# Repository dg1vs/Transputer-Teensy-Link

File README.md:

# Transputer Teensy Link

A family of practical, Ethernet-connected link interfaces for classic INMOS transputer systems, based on the Teensy 4.1.

The project provides three hardware variants, a common firmware platform, and compatibility with host tools using the INMOS B300/TCPlink protocol.

> **Project status:** All three interfaces are in active use. They are experimental retrocomputing hardware and may still contain minor hardware or firmware quirks. Enclosures have not yet been designed.

## Why transputers are still interesting in 2026

Transputers remain fascinating devices even in 2026.

They combine a processor, local memory, hardware-assisted process scheduling, and fast point-to-point communication links. A transputer was intended to be used as a building block in a larger network of cooperating processors rather than as the single centre of a computer.

Together with occam and its CSP-inspired programming model, transputers provide a very direct platform for studying:

- concurrent and parallel programming;
- message passing;
- distributed systems;
- deterministic communication;
- hardware-supported process scheduling;
- processor networks without a shared system bus.

Many of these ideas are still relevant in modern many-core processors, network-on-chip architectures, distributed services, and accelerator systems.

The difficult part today is often not finding an interesting transputer board. The practical problem is finding a convenient interface between a modern computer and the transputer link.

## Design goals

A useful modern transputer link interface should ideally be:

- **Fast** — supporting the maximum 20 Mbit/s link speed.
- **Standards-based** — using a documented and already supported host interface.
- **Galvanically isolated** — at least between the development computer and the adapter.
- **Cross-platform** — usable from Linux, macOS, Windows, and other systems.
- **Based on available components** — without requiring rare historical devices such as the INMOS C011.
- **Practical** — compact, robust, and easy to connect to different target systems.

The use of Ethernet provides a standard host connection and, with normal Ethernet magnetics, galvanic isolation between the host network and the adapter.

The current transputer-side interfaces are single-ended and share their electrical reference with the target system. Full galvanic isolation of the transputer link itself is therefore a possible future improvement rather than a feature of the current boards.

## Project history

Andre Saischowa created the first prototype using a Teensy 4.1 together with an INMOS C011 link adapter.

The article [Putting A Teensy To Task As A Transputer Link](https://hackaday.com/2025/10/20/putting-a-teensy-to-task-as-a-transputer-link/) described how the Teensy 4.1 UART can implement the unusual transputer link framing directly. This led to a substantial extension of the firmware and made it possible to operate a transputer link without a C011.

Karsten Schmidt, DG1VS, designed the printed circuit boards. Andre is the author and maintainer of the Teensy Link software and continued to develop and improve the firmware.

The result is a common software platform supporting both the traditional C011 approach and direct Teensy-to-transputer communication.

## System overview

```mermaid
flowchart LR
    HOST["Host computer<br/>Linux, macOS, Windows, ..."]
    ETH["Ethernet / TCP/IP<br/>B300-compatible Linkops service"]
    T41["Teensy 4.1"]
    PHY["C011 or direct<br/>transputer link"]
    TARGET["Transputer system"]

    HOST <--> ETH
    ETH <--> T41
    T41 <--> PHY
    PHY <--> TARGET
```

The firmware obtains its IP address using DHCP and provides a B300-compatible service on TCP port **4047**.

The current firmware also contains:

- a small status web server on TCP port **80**;
- a network throughput test service on TCP port **4040**;
- optional SSD1306 OLED status output;
- experimental USB host, USB MIDI, and link-audio functions.

The additional USB and audio functions are not required for normal B300 link operation.

## Hardware variants

The KiCad hardware projects are located below [`hardware/`](hardware/).

### A. `link_teensy` — C011 and direct Teensy Link

Directory: [`hardware/link_teensy/`](hardware/link_teensy/)

This is the most complete board and contains both:

- a traditional INMOS C011 link interface;
- a direct Teensy 4.1 transputer link interface.

```mermaid
flowchart LR
    HOST["Ethernet host"] <--> T41["Teensy 4.1"]
    T41 --> C011["INMOS C011"]
    T41 --> DIRECT["Direct Teensy Link"]
    C011 --> TARGET["Transputer system"]
    DIRECT --> TARGET
```

This board is useful as:

- the original development platform;
- a C011 reference implementation;
- a comparison between C011 and direct UART-based link handling;
- a flexible laboratory interface.

The main disadvantage of the C011 path is its dependency on a historical component that is increasingly difficult to obtain.

### B. `link_teensy_small` — compact direct link

Directory: [`hardware/link_teensy_small/`](hardware/link_teensy_small/)

This is a smaller board that connects the Teensy 4.1 directly to the transputer link without requiring a C011.

```mermaid
flowchart LR
    HOST["Ethernet host"] <--> T41["Teensy 4.1"]
    T41 <--> TARGET["Transputer system"]
```

This is currently the most frequently used interface.

Its advantages include:

- no historical link-adapter IC;
- fewer components;
- compact construction;
- direct 20 Mbit/s operation;
- a 10-pin target connector carrying the link and subsystem control signals.

The target connector includes:

- `LinkIn`
- `LinkOut`
- `notReset`
- `notAnalyse`
- `notError`
- supply and ground connections

Always verify the exact connector orientation and board revision before connecting a target.

### C. `link_teensy_fpga` — direct link with PMOD adapter

Directory: [`hardware/link_teensy_fpga/`](hardware/link_teensy_fpga/)

This version is derived from the compact direct-link design and adds a 12-pin PMOD-style connector.

It is currently used while developing the [Transputer Picoputer](https://github.com/dg1vs/Transputer-Picoputer).

```mermaid
flowchart LR
    HOST["Ethernet host"] <--> T41["Teensy 4.1"]
    T41 <--> PMOD["PMOD adapter"]
    PMOD <--> PICOPUTER["Transputer Picoputer"]
```

The PMOD mapping documented in the schematic is:

| Transputer signal | PMOD pin | Transputer signal | PMOD pin |
|---|---:|---|---:|
| `LinkIn` | 1 | `LinkOut` | 7 |
| `notAnalyse` | 2 | `notReset` | 8 |
| — | 3 | `notError` | 9 |
| — | 4 | — | 10 |
| GND | 5 | GND | 11 |
| 3.3 V | 6 | 3.3 V | 12 |

This variant is intended for development systems that expose their transputer-style link through a PMOD-compatible connector.

## How the direct Teensy Link works

The INMOS transputer link protocol resembles asynchronous serial communication, but it is not a conventional UART protocol.

Two token types are used:

- an **11-bit data token** carrying one byte;
- a very short **2-bit acknowledgement token**.

The Teensy 4.1 UART provides two features that make a direct implementation possible:

- inverted transmit and receive operation;
- 9-bit UART data mode.

The additional UART bit is used to reproduce the special transputer data-token framing. Incoming words are decoded as either data or acknowledgements, and the firmware implements the required link-level handshake and buffering.

The current direct-link implementation supports:

- **5 Mbit/s** as an available code path;
- **20 Mbit/s** as the normal and default operating mode.

The firmware deliberately rejects **10 Mbit/s** and recommends 20 Mbit/s. At the maximum speed, a timing corner case involving the emulated acknowledgement and a very fast response to operations such as `PEEK` is avoided.

The direct-link implementation currently uses:

| Function | Teensy 4.1 resource |
|---|---|
| Link UART | `Serial7` |
| Receive | pin 28 |
| Transmit | pin 29 |
| Target reset | pin 30 |
| Target analyse | pin 31 |
| Target error | pin 32 |

These assignments are defined in [`firmware/teensy_audiomidi_c011/tplinkconf.h`](firmware/teensy_audiomidi_c011/tplinkconf.h).

## B300 compatibility

The original INMOS IMS B300 TCPlink system provided network access to transputer links over Ethernet and TCP/IP.

This project implements the relevant **Linkops** service used by B300-compatible host drivers. The implemented operations include:

- open and close link;
- write and read link data;
- reset;
- analyse;
- test error.

The firmware identifies the service as:

```text
inmos.com(tcplink-linkops-01.00)
```

The B300-compatible server listens on the standard TCP port:

```text
4047
```

Technical documentation for the original system is available from transputer.net:

- [IMS B300 TCPlink Development System](https://www.transputer.net/mg/300/1857.pdf)
- [transputer.net documentation archive](https://www.transputer.net/)

## Host software

Modern builds of classic transputer host tools and the `link300` driver are provided by Michael through transputer.net:

- [bin.transputer.net](https://bin.transputer.net/)
- [binary archive](https://bin.transputer.net/bin2/)

Michael is the owner and maintainer of the tools distributed through transputer.net. These host tools are separate from the Teensy Link firmware in this repository.

Packages are available for several systems and architectures, including:

- Linux: x86, x86-64, ARM, AArch64, MIPS, and PowerPC;
- macOS: Intel x86-64 and Apple Silicon ARM64;
- Windows: x86, x86-64, ARM, and ARM64;
- DOS and several other historical operating systems.

Depending on the platform, the archive contains tools such as:

- `iserver`
- `afserver`
- `linktest`
- `peek`
- `poke`
- `rspy`
- `analyse`
- the `link300` library or DLL

The [`software/`](software/) directory contains project notes. For current binaries, use the transputer.net archive directly and observe its licensing and redistribution conditions.

## Firmware

The main firmware is located in:

[`firmware/teensy_audiomidi_c011/`](firmware/teensy_audiomidi_c011/)

A separate pin-test sketch is located in:

[`firmware/teensy_pin_test/`](firmware/teensy_pin_test/)

### Current default configuration

The checked-in [`tplinkconf.h`](firmware/teensy_audiomidi_c011/tplinkconf.h) currently enables:

- direct Teensy Link;
- Ethernet and B300 service;
- USB host support;
- USB MIDI client support;
- a 128 × 64 SSD1306 OLED at I²C address `0x3c`.

The C011 backend is present but disabled in the default configuration.

### Selecting the link backend

For the direct Teensy Link:

```cpp
//#define MIT_LINK_C011
#define MIT_LINK_TEENSY
```

For the C011 backend, enable `MIT_LINK_C011` and configure the other options according to the connected hardware.

The firmware can contain both backends, but their exact routing behaviour depends on the selected compile-time options. Review `tplinkconf.h` before building.

## Building the firmware

The firmware is intended for a **Teensy 4.1** using the Arduino IDE with Teensy support.

### Requirements

Install the following:

- Arduino IDE;
- Teensy board support / Teensyduino;
- `NativeEthernet`;
- `LibPrintf`;
- `Adafruit GFX Library`;
- `Adafruit SSD1306`.

The Teensy core USB host library is used by the optional USB host functions.

### Enable 9-bit UART support

The direct transputer link requires 9-bit UART support in the Teensy core.

Locate `HardwareSerial.h` in the installed Teensy 4 core and enable:

```cpp
#define SERIAL_9BIT_SUPPORT
```

The firmware checks for the resulting 9-bit inverted-UART definitions and stops compilation with an explanatory error when they are unavailable.

This modification may need to be repeated after updating the Teensy board package.

### Arduino USB type

The checked-in configuration enables the USB MIDI client code. Select an Arduino USB type that provides both **Serial** and **MIDI**, or disable `MIT_USBMIDI_CLIENT` in `tplinkconf.h`.

### Upload and startup

1. Open:

   ```text
   firmware/teensy_audiomidi_c011/teensy_audiomidi_c011.ino
   ```

2. Select **Teensy 4.1** as the target board.

3. Review `tplinkconf.h`.

4. Compile and upload the sketch.

5. Connect Ethernet.

6. Open the serial monitor or read the optional OLED display.

The adapter uses DHCP and reports its assigned IP address through the serial console and OLED display.

The serial startup message also shows:

- the selected link implementation;
- the 20 Mbit/s link initialization;
- the B300 port;
- the web-monitor port;
- the speed-test port.

## Connecting host tools

The exact setup depends on the operating system and the downloaded `link300` driver.

A typical Linux example is:

```bash
export TRANSPUTER="$HOME/bin/transputer/link300.so.1.0.1@192.168.1.123"
```

Replace:

- the library path with the actual location and filename;
- `192.168.1.123` with the IP address shown by the adapter.

You can then test the connection using tools such as:

```bash
linktest
```

or inspect a connected network with:

```bash
rspy
```

To boot a transputer program:

```bash
iserver -sb program.btl
```

Tool names, options, and library filenames vary slightly between operating systems and architectures.

Only one B300 client should normally control the adapter link at a time.

## Network services

| Port | Function |
|---:|---|
| `4047/tcp` | B300-compatible Linkops service |
| `4040/tcp` | experimental network throughput test |
| `80/tcp` | simple status and monitoring web page |

The status page can be opened in a browser using the adapter IP address:

```text
http://192.168.1.123/
```

The web page is a development monitor, not a hardened management interface. The adapter should therefore be used on a trusted local network.

## Repository structure

```text
Transputer-Teensy-Link/
├── docs/
│   └── README.md
├── firmware/
│   ├── teensy_audiomidi_c011/
│   ├── teensy_pin_test/
│   └── README.md
├── hardware/
│   ├── docu_extern/
│   ├── libs/
│   ├── link_teensy/
│   ├── link_teensy_small/
│   ├── link_teensy_fpga/
│   └── README.md
├── software/
│   ├── README.md
│   └── bin.zip
├── .gitmodules
└── README.md
```

The KiCad projects use the external
[Transputer KiCad Library](https://github.com/dg1vs/Transputer-Kicad-Library)
as a Git submodule.

Clone the project with submodules:

```bash
git clone --recurse-submodules git@github.com:dg1vs/Transputer-Teensy-Link.git
```

For an existing clone:

```bash
git submodule update --init --recursive
```

The hardware files are current KiCad 9 projects.

## Current limitations and open work

The interfaces are working development tools, but the following points remain:

- the hardware and firmware may still contain minor quirks;
- documentation is still being expanded;
- some firmware modules are experimental;
- the web interface has no authentication;
- the direct target link is not galvanically isolated;
- board-specific assembly and connector documentation should be checked carefully;
- enclosures still need to be designed.

## Safety and hardware notes

Before applying power:

- check the schematic for the exact board revision;
- verify the target voltage and connector orientation;
- verify `LinkIn` and `LinkOut`;
- verify `notReset`, `notAnalyse`, and `notError`;
- check whether the target supplies the adapter or the adapter supplies the target;
- avoid powering the Teensy simultaneously from incompatible USB and external sources;
- follow the schematic notes concerning separation of `VIN` and `VUSB`.

Classic transputer hardware is increasingly difficult to replace. Test new cables and boards with current-limited supplies before connecting valuable systems.

## Related resources

- [Transputer Teensy Link](https://github.com/dg1vs/Transputer-Teensy-Link)
- [Transputer Picoputer](https://github.com/dg1vs/Transputer-Picoputer)
- [Hackaday: Putting A Teensy To Task As A Transputer Link](https://hackaday.com/2025/10/20/putting-a-teensy-to-task-as-a-transputer-link/)
- [8 Bit Force: Teensy 4.1 speaks Transputer Link](https://www.8bitforce.com/blog/2025/10/02/teensy-4.1-speaks-transputer-link/)
- [IMS B300 TCPlink Development System](https://www.transputer.net/mg/300/1857.pdf)
- [transputer.net](https://www.transputer.net/)
- [transputer.net binary archive](https://bin.transputer.net/bin2/)

## Contributions

Feedback, documentation improvements, test reports, and fixes are welcome.

A useful issue report should include:

- hardware variant and board revision;
- Teensy firmware Git commit;
- active options from `tplinkconf.h`;
- transputer type and clock frequency;
- link speed;
- host operating system and CPU architecture;
- host tool and `link300` version;
- target connector and cable details;
- serial console output;
- a clear description of the observed behaviour.

## Disclaimer

This is an experimental retrocomputing project and is provided without warranty. Verify all electrical characteristics before connecting the adapter to valuable or irreplaceable hardware.

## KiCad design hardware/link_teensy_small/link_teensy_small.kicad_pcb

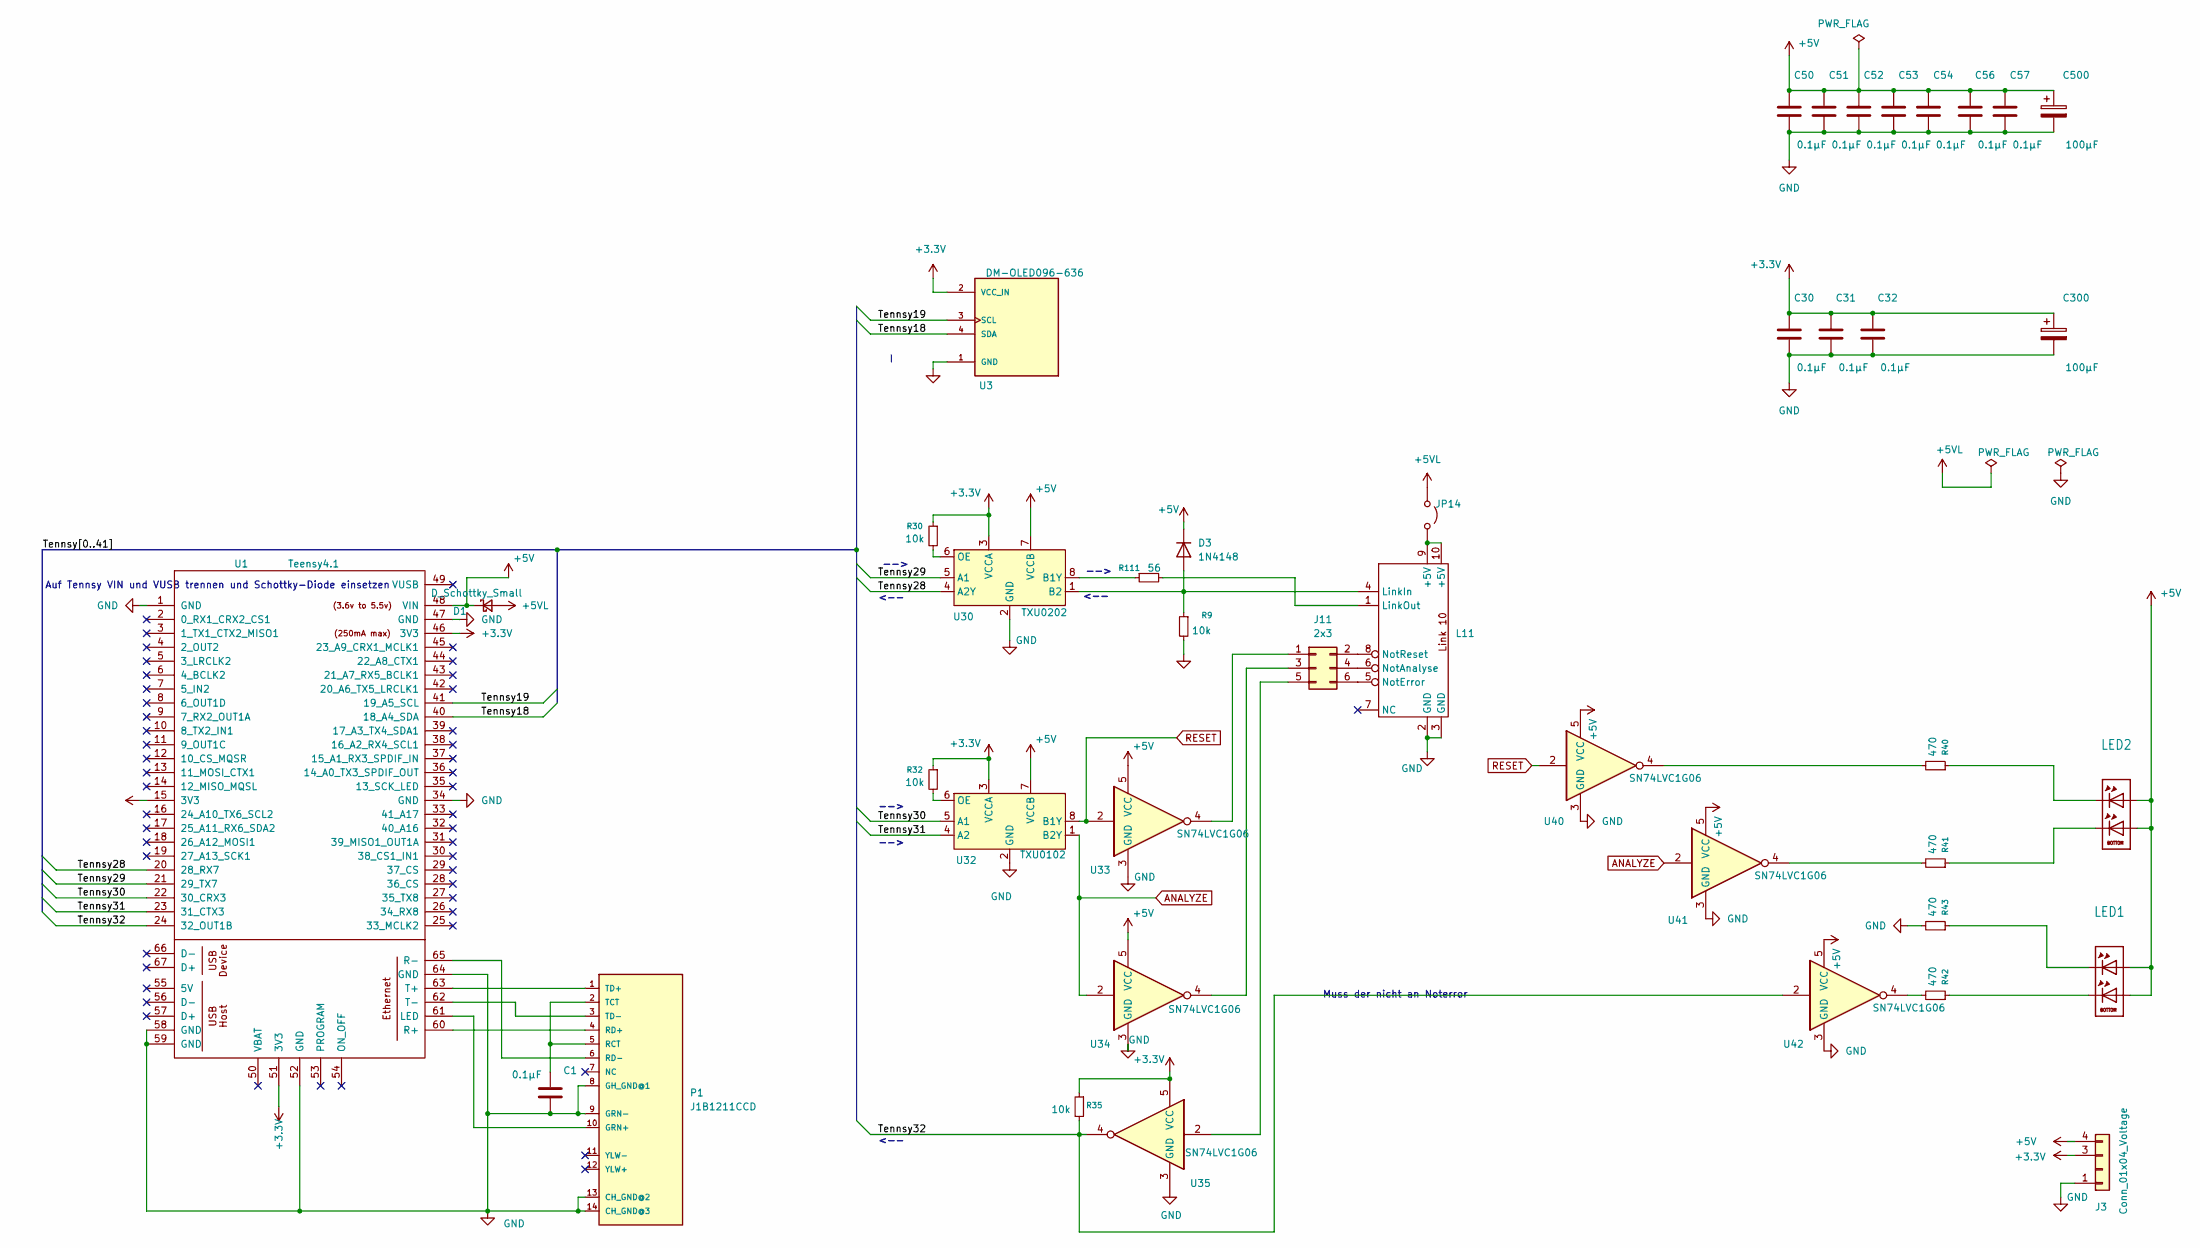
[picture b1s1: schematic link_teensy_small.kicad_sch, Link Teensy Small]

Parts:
C1, C30, C31, C32, C50, C51, C52, C53, C54, C56, C57: 0.1µF; C_0603_1608Metric_Pad1.08x0.95mm_HandSolder
C300, C500: 100µF; CP_Elec_5x3.9
D1: D_Schottky_Small; D_SMB
D3: 1N4148; D_SOD-323_HandSoldering
J3: Conn_01x04_Voltage; PinHeader_1x04_P2.54mm_Vertical
J11: 2x3; PinHeader_2x03_P2.54mm_Vertical
JP14: Jumper_2_Open; PinHeader_1x02_P2.54mm_Vertical
L11: IDC-Header_2x05_P2.54mm_Horizontal
LED1, LED2: mentor_LED_2
P1: J1B1211CCD
R9, R30, R32, R35: 10k; R_0603_1608Metric_Pad0.98x0.95mm_HandSolder
R40, R41, R42, R43: 470; R_0603_1608Metric_Pad0.98x0.95mm_HandSolder
R111: 56; R_0603_1608Metric_Pad0.98x0.95mm_HandSolder
U1: Teensy4.1; Teensy41
U3: DM-OLED096-636; MODULE_DM-OLED096-636
U30: TXU0202; VSSOP-8_2.3x2mm_P0.5mm
U32: TXU0102; VSSOP-8_2.3x2mm_P0.5mm
U33, U34, U35, U40, U41, U42: SN74LVC1G06; SOT-23-5_HandSoldering

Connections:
+3.3V: C30.1, C31.1, C32.1, C300.1, J3.3, R30.1, R32.1, R35.1, U1.15 (3V3), U1.46 (3V3), U1.51 (3V3), U3.2 (VCC_IN), U30.3 (VCCA), U32.3 (VCCA), U35.5 (VCC)
+5V: C50.1, C51.1, C52.1, C53.1, C54.1, C56.1, C57.1, C500.1, D1.1 (K), D3.1 (K), J3.4, LED1.A1 (A2), LED1.A2, LED2.A1 (A2), LED2.A2, U1.48 (VIN), U30.7 (VCCB), U32.7 (VCCB), U33.5 (VCC), U34.5 (VCC), U40.5 (VCC), U41.5 (VCC), U42.5 (VCC)
+5VL: D1.2 (A), JP14.1 (A)
/Tennsy18: U1.40 (18_A4_SDA), U3.4 (SDA)
/Tennsy19: U1.41 (19_A5_SCL), U3.3 (SCL)
/Tennsy28: U1.20 (28_RX7), U30.4 (A2Y)
/Tennsy29: U1.21 (29_TX7), U30.5 (A1)
/Tennsy30: U1.22 (30_CRX3), U32.5 (A1)
/Tennsy31: U1.23 (31_CTX3), U32.4 (A2)
/Tennsy32: R35.2, U1.24 (32_OUT1B), U35.4, U42.2
ANALYZE: U32.1 (B2Y), U34.2, U41.2
GND: C1.2, C30.2, C31.2, C32.2, C50.2, C51.2, C52.2, C53.2, C54.2, C56.2, C57.2, C300.2, C500.2, J3.1, L11.2 (GND), L11.3 (GND), P1.8 (GH_GND@1), P1.9 (GRN-), P1.13 (CH_GND@2), P1.14 (CH_GND@3), R9.2, R43.2, U1.1 (GND), U1.34 (GND), U1.47 (GND), U1.52 (GND), U1.58 (GND), U1.59 (GND), U1.64 (GND), U3.1 (GND), U30.2 (GND), U32.2 (GND), U33.3 (GND), U34.3 (GND), U35.3 (GND), U40.3 (GND), U41.3 (GND), U42.3 (GND)
unnamed: D3.2 (A), L11.4 (LinkIn), R9.1, U30.1 (B2)
unnamed: J11.1, U33.4
unnamed: J11.2, L11.8 (NotReset)
unnamed: J11.3, U34.4
unnamed: J11.4, L11.6 (NotAnalyse)
unnamed: J11.5, U35.2
unnamed: J11.6, L11.5 (NotError)
unnamed: JP14.2 (B), L11.9 (+5V), L11.10 (+5V)
unnamed: L11.1 (LinkOut), R111.2
unnamed: LED1.C1, R42.1
unnamed: LED1.C2, R43.1
unnamed: LED2.C1, R41.1
unnamed: LED2.C2, R40.1
unnamed: P1.10 (GRN+), U1.61 (LED)
unnamed: C1.1, P1.2 (TCT), P1.5 (RCT)
unnamed: P1.4 (RD+), U1.60 (R+)
unnamed: P1.6 (RD-), U1.65 (R-)
unnamed: P1.1 (TD+), U1.63 (T+)
unnamed: P1.3 (TD-), U1.62 (T-)
unnamed: R40.2, U40.4
unnamed: R41.2, U41.4
unnamed: R42.2, U42.4
unnamed: R111.1, U30.8 (B1Y)
unnamed: R30.2, U30.6 (OE)
unnamed: R32.2, U32.6 (OE)
RESET: U32.8 (B1Y), U33.2, U40.2

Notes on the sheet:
Auf Tennsy VIN und VUSB trennen und Schottky-Diode einsetzen
-->
<--
Muss der nicht an Noterror

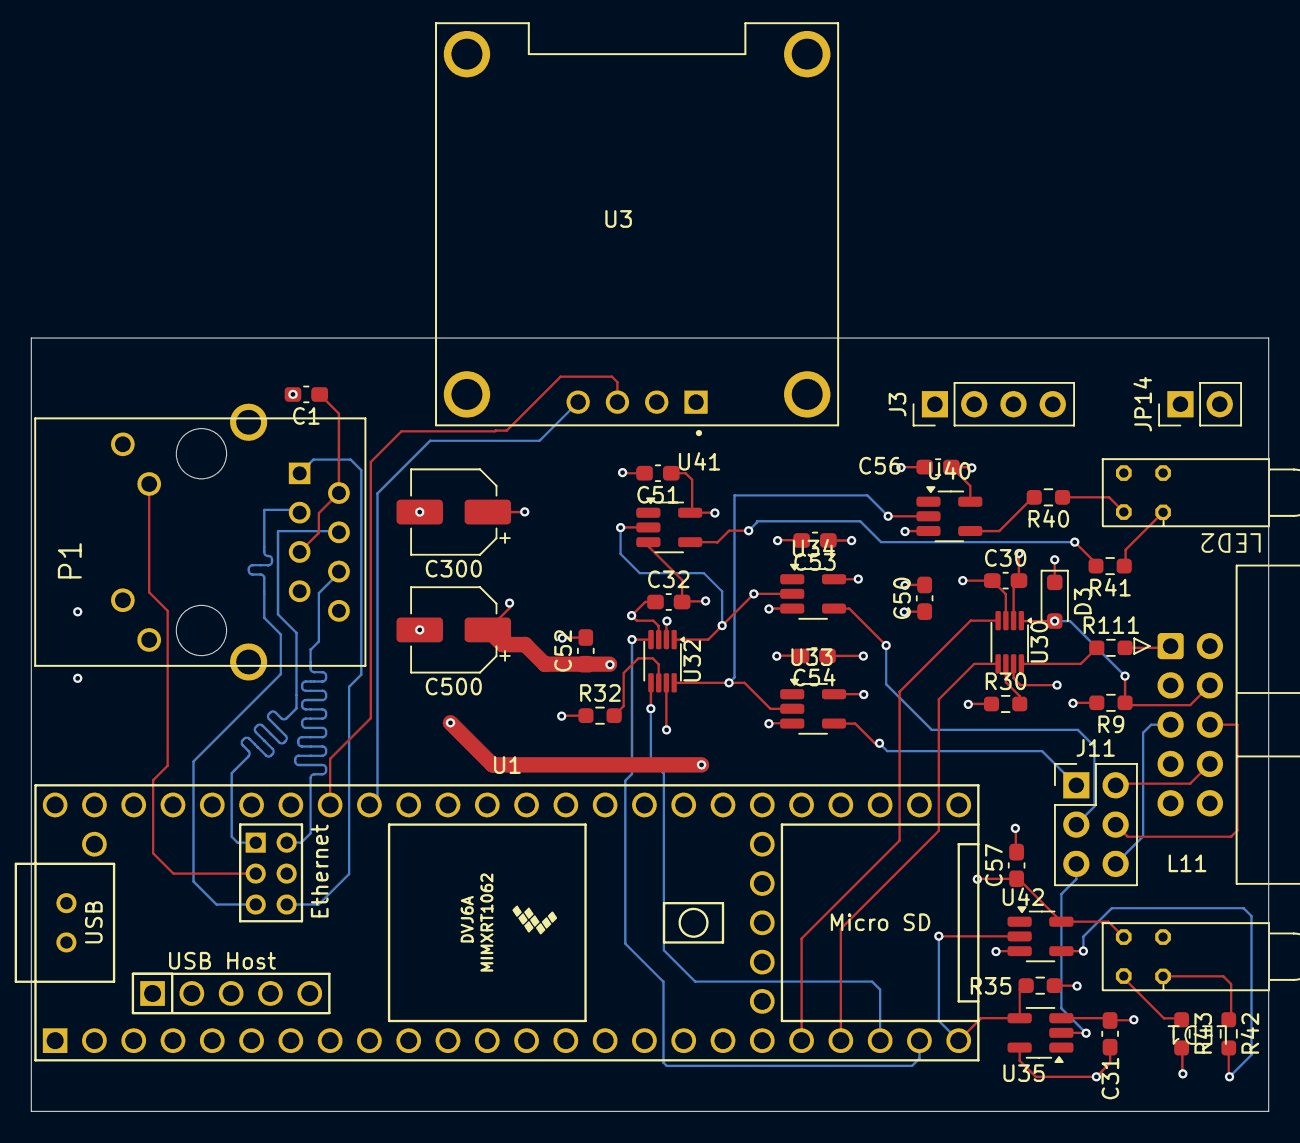
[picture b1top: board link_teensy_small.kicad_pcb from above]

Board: 4 copper layers, 80.0 x 50.0 mm, 41 parts (1 on the bottom side), 38 nets.

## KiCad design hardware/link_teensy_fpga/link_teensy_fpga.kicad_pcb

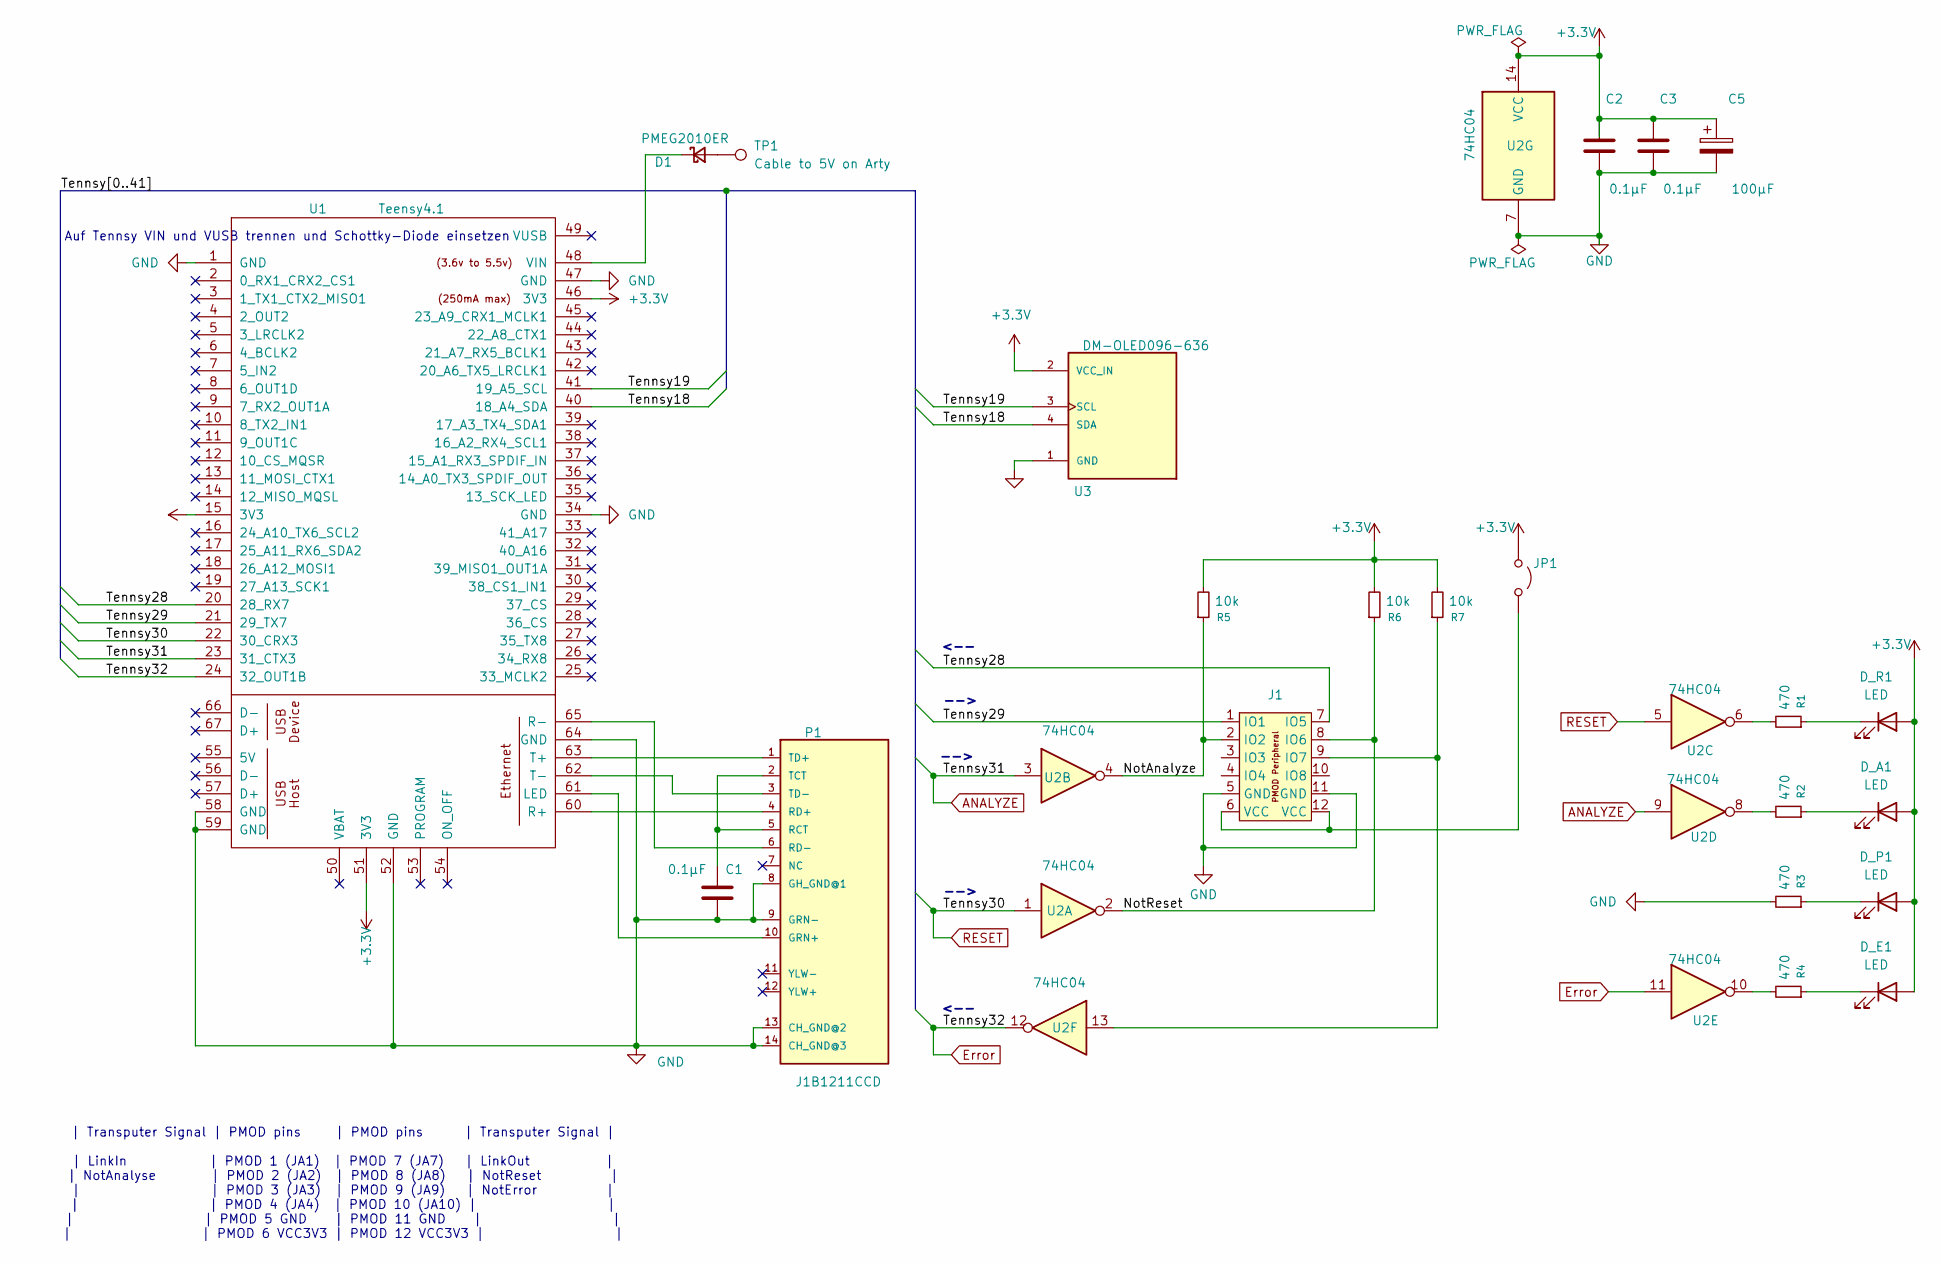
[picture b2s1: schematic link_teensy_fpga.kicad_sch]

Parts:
C1, C2, C3: 0.1µF; C_0603_1608Metric_Pad1.08x0.95mm_HandSolder
C5: 100µF; CP_Elec_5x3.9
D1: PMEG2010ER; Nexperia_CFP3_SOD-123W
D_A1: LED; LED_D3.0mm
D_E1: LED; LED_D3.0mm
D_P1: LED; LED_D3.0mm
D_R1: LED; LED_D3.0mm
J1: PinHeader_2x06_P2.54mm_PMODPeriph2B
JP1: Jumper_2_Open; PinHeader_1x02_P2.54mm_Vertical
P1: J1B1211CCD
R1, R2, R3, R4: 470; R_0603_1608Metric_Pad0.98x0.95mm_HandSolder
R5, R6, R7: 10k; R_0603_1608Metric_Pad0.98x0.95mm_HandSolder
TP1: Cable to 5V on Arty; PinHeader_1x01_P2.54mm_Vertical
U1: Teensy4.1; Teensy41
U2: 74HC04; SOIC-14_3.9x8.7mm_P1.27mm
U3: DM-OLED096-636; MODULE_DM-OLED096-636

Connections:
+3.3V: C2.1, C3.1, C5.1, D_A1.2 (A), D_E1.2 (A), D_P1.2 (A), D_R1.2 (A), JP1.1 (A), R5.2, R6.2, R7.2, U1.15 (3V3), U1.46 (3V3), U1.51 (3V3), U2.14 (VCC), U3.2 (VCC_IN)
/NotAnalyze: J1.2 (IO2), R5.1, U2.4
/NotReset: J1.8 (IO6), R6.1, U2.2
/Tennsy18: U1.40 (18_A4_SDA), U3.4 (SDA)
/Tennsy19: U1.41 (19_A5_SCL), U3.3 (SCL)
/Tennsy28: J1.7 (IO5), U1.20 (28_RX7)
/Tennsy29: J1.1 (IO1), U1.21 (29_TX7)
ANALYZE: U1.23 (31_CTX3), U2.3, U2.9
Error: U1.24 (32_OUT1B), U2.11, U2.12
GND: C1.2, C2.2, C3.2, C5.2, J1.5 (GND), J1.11 (GND), P1.8 (GH_GND@1), P1.9 (GRN-), P1.13 (CH_GND@2), P1.14 (CH_GND@3), R3.2, U1.1 (GND), U1.34 (GND), U1.47 (GND), U1.52 (GND), U1.58 (GND), U1.59 (GND), U1.64 (GND), U2.7 (GND), U3.1 (GND)
unnamed: D1.2 (A), TP1.1 (1_1)
unnamed: D1.1 (K), U1.48 (VIN)
unnamed: D_A1.1 (K), R2.1
unnamed: D_E1.1 (K), R4.1
unnamed: D_P1.1 (K), R3.1
unnamed: D_R1.1 (K), R1.1
unnamed: J1.9 (IO7), R7.1, U2.13
unnamed: J1.6 (VCC), J1.12 (VCC), JP1.2 (B)
unnamed: P1.10 (GRN+), U1.61 (LED)
unnamed: C1.1, P1.2 (TCT), P1.5 (RCT)
unnamed: P1.4 (RD+), U1.60 (R+)
unnamed: P1.6 (RD-), U1.65 (R-)
unnamed: P1.1 (TD+), U1.63 (T+)
unnamed: P1.3 (TD-), U1.62 (T-)
unnamed: R1.2, U2.6
unnamed: R2.2, U2.8
unnamed: R4.2, U2.10
RESET: U1.22 (30_CRX3), U2.1, U2.5

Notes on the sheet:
Auf Tennsy VIN und VUSB trennen und Schottky-Diode einsetzen
| Transputer Signal | PMOD pins | PMOD pins | Transputer Signal | | LinkIn | PMOD 1 (JA1) | PMOD 7 (JA7) | LinkOut | | NotAnalyse | PMOD 2 (JA2) | PMOD 8 (JA8) | NotReset | | | PMOD 3 (JA3) | PMOD 9 (JA9) | NotError | | | PMOD 4 (JA4) | PMOD 10 (JA10) | | | | PMOD 5 GND | PMOD 11 GND | | | | PMOD 6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
-->
<--

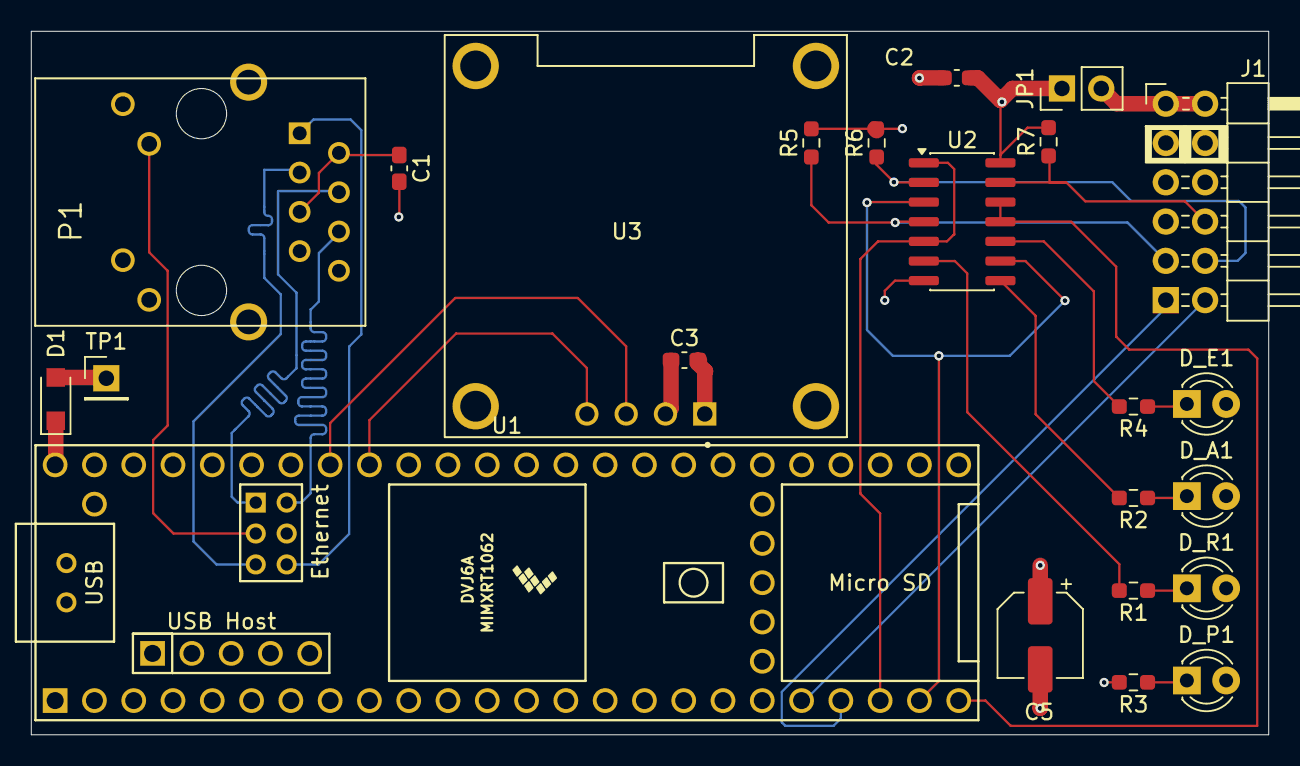
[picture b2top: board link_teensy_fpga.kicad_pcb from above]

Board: 4 copper layers, 80.0 x 45.5 mm, 23 parts (0 on the bottom side), 28 nets.
